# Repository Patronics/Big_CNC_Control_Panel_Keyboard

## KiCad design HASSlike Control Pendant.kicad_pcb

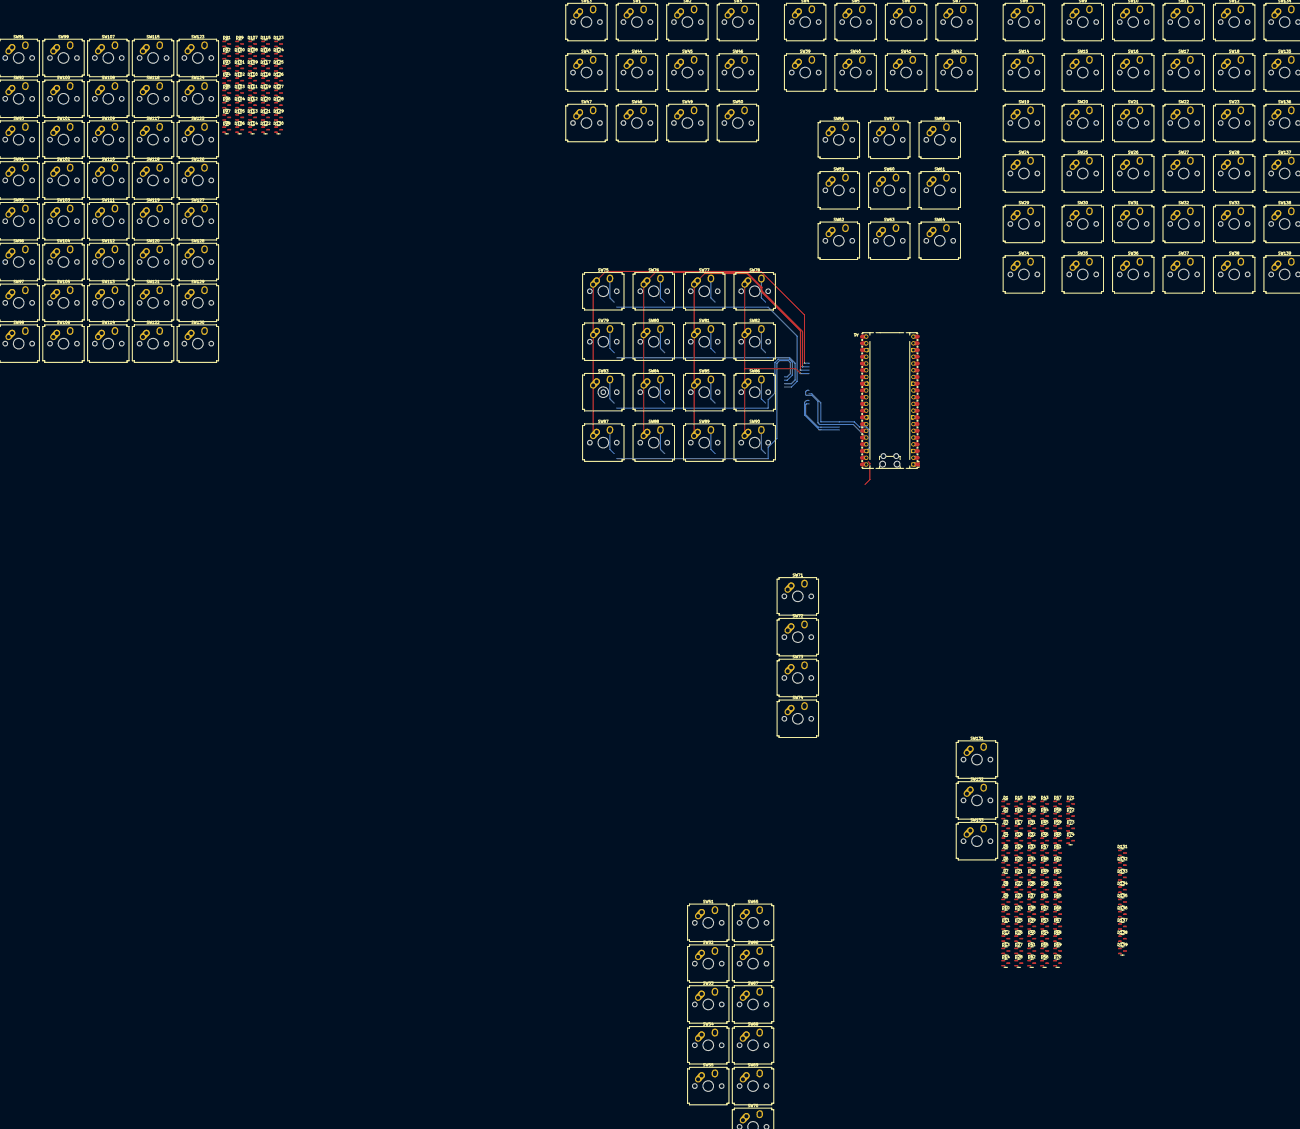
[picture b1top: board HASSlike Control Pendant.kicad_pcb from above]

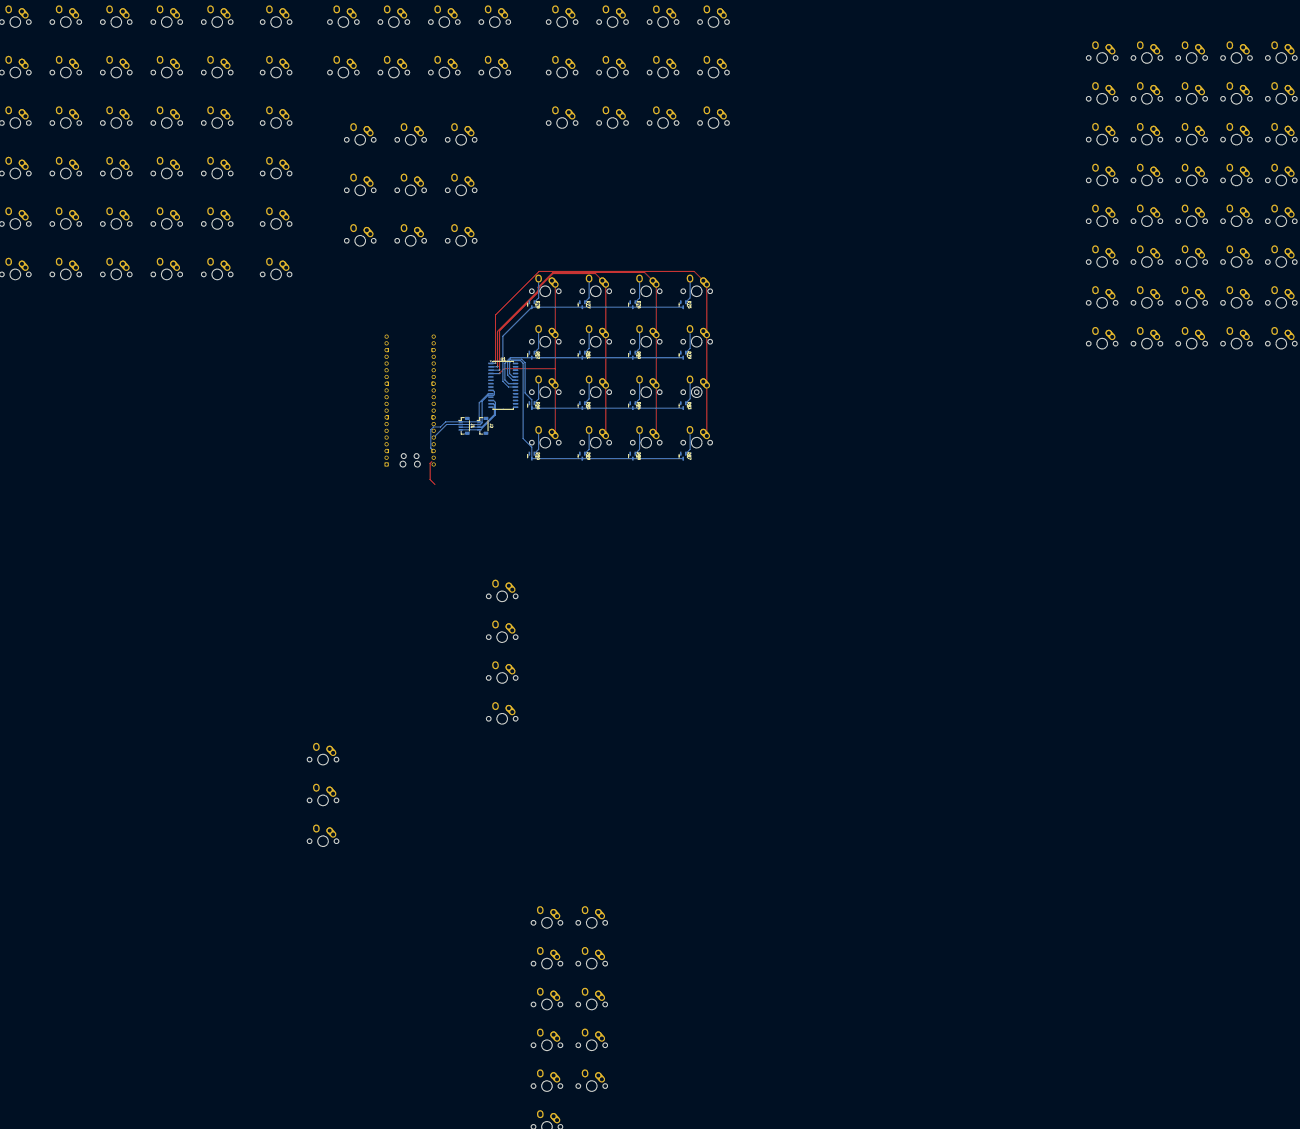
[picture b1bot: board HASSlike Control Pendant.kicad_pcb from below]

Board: 2 copper layers, 282 parts (19 on the bottom side), 184 nets.

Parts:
A1: RaspberryPi_Pico_W; RaspberryPi_Pico_Common_Unspecified
D1, D2, D3, D4, D5, D6, D7, D8, D9, D10, D11, D12, D13, D14, D15, D16, D17, D18, D19, D20, D21, D22, D23, D24, D25, D26, D27, D28, D29, D30, D31, D32, D33, D34, D35, D36, D37, D38, D39, D40, D41, D42, D43, D44, D45, D46, D47, D48, D49, D50, D51, D52, D53, D54, D55, D56, D57, D58, D59, D60, D61, D62, D63, D64, D65, D66, D67, D68, D69, D70, D71, D72, D73, D74, D75, D76, D77, D78, D79, D80, D81, D82, D83, D84, D85, D86, D87, D88, D89, D90, D91, D92, D93, D94, D95, D96, D97, D98, D99, D100, D101, D102, D103, D104, D105, D106, D107, D108, D109, D110, D111, D112, D113, D114, D115, D116, D117, D118, D119, D120, D121, D122, D123, D124, D125, D126, D127, D128, D129, D130, D131, D132, D133, D134, D135, D136, D137, D138, D139: D_Small; D_SOT-23_MMDB4148_BAS21_BAT54
J1, J2: Conn_01x04_Pin; JST_SH_BM04B-SRSS-TB_1x04-1MP_P1.00mm_Vertical
SW1, SW2, SW3, SW4, SW5, SW6, SW7, SW8, SW9, SW10, SW11, SW12, SW13, SW14, SW15, SW16, SW17, SW18, SW19, SW20, SW21, SW22, SW23, SW24, SW25, SW26, SW27, SW28, SW29, SW30, SW31, SW32, SW33, SW34, SW35, SW36, SW37, SW38, SW39, SW40, SW41, SW42, SW43, SW44, SW45, SW46, SW47, SW48, SW49, SW50, SW51, SW52, SW53, SW54, SW55, SW56, SW57, SW58, SW59, SW60, SW61, SW62, SW63, SW64, SW65, SW66, SW67, SW68, SW69, SW70, SW71, SW72, SW73, SW74, SW75, SW76, SW77, SW78, SW79, SW80, SW81, SW82, SW83, SW84, SW85, SW86, SW87, SW88, SW89, SW90, SW91, SW92, SW93, SW94, SW95, SW96, SW97, SW98, SW99, SW100, SW101, SW102, SW103, SW104, SW105, SW106, SW107, SW108, SW109, SW110, SW111, SW112, SW113, SW114, SW115, SW116, SW117, SW118, SW119, SW120, SW121, SW122, SW123, SW124, SW125, SW126, SW127, SW128, SW129, SW130, SW131, SW132, SW133, SW134, SW135, SW136, SW137, SW138, SW139: SW_Push; SW_Hybrid_Cherry_MX_Alps_1.00u
U1: MCP23017_SO; SOIC-28W_7.5x17.9mm_P1.27mm

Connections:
/4x4Test/Col1: SW75.1, SW79.1, SW83.1, SW87.1, U1.1 (GPB0)
/4x4Test/Col2: SW76.1, SW80.1, SW84.1, SW88.1, U1.2 (GPB1)
/4x4Test/Col3: SW77.1, SW81.1, SW85.1, SW89.1, U1.3 (GPB2)
/4x4Test/Col4: SW78.1, SW82.1, SW86.1, SW90.1, U1.4 (GPB3)
/4x4Test/Row1: D75.1 (K), D76.1 (K), D77.1 (K), D78.1 (K), U1.21 (GPA0)
/4x4Test/Row2: D79.1 (K), D80.1 (K), D81.1 (K), D82.1 (K), U1.22 (GPA1)
/4x4Test/Row3: D83.1 (K), D84.1 (K), D85.1 (K), D86.1 (K), U1.23 (GPA2)
/4x4Test/Row4: D87.1 (K), D88.1 (K), D89.1 (K), D90.1 (K), U1.24 (GPA3)
/SCL: J1.4, J2.4, U1.12 (SCK)
/SDA: J1.3, J2.3, U1.13 (SDA)
COL1: SW13.1, SW43.1, SW47.1, SW51.1, SW65.1, SW70.1
COL2: SW1.1, SW44.1, SW48.1, SW52.1, SW66.1, SW71.1
COL3: SW2.1, SW45.1, SW49.1, SW53.1, SW67.1, SW72.1
COL4: SW3.1, SW46.1, SW50.1, SW54.1, SW68.1, SW73.1
COL5: SW4.1, SW39.1, SW55.1, SW69.1, SW74.1
COL6: SW5.1, SW40.1, SW56.1, SW59.1, SW62.1, SW131.1
COL7: SW6.1, SW41.1, SW57.1, SW60.1, SW63.1, SW132.1
COL8: SW7.1, SW42.1, SW58.1, SW61.1, SW64.1, SW133.1
COL9: SW8.1, SW14.1, SW19.1, SW24.1, SW29.1, SW34.1
COL10: SW9.1, SW15.1, SW20.1, SW25.1, SW30.1, SW35.1
COL11: SW10.1, SW16.1, SW21.1, SW26.1, SW31.1, SW36.1
COL12: SW11.1, SW17.1, SW22.1, SW27.1, SW32.1, SW37.1
COL13: SW12.1, SW18.1, SW23.1, SW28.1, SW33.1, SW38.1
COL14: SW134.1, SW135.1, SW136.1, SW137.1, SW138.1, SW139.1
GND: A1.3 (GND), A1.8 (GND), A1.13 (GND), A1.18 (GND), A1.23 (GND), A1.28 (GND), A1.38 (GND), J1.1, J2.1, U1.10 (VSS)
unnamed: D1.2 (A), SW13.2
unnamed: D2.2 (A), SW1.2
unnamed: D3.2 (A), SW2.2
unnamed: D4.2 (A), SW3.2
unnamed: D5.2 (A), SW4.2
unnamed: D6.2 (A), SW5.2
unnamed: D7.2 (A), SW6.2
unnamed: D8.2 (A), SW7.2
unnamed: D9.2 (A), SW8.2
unnamed: D10.2 (A), SW9.2
unnamed: D11.2 (A), SW10.2
unnamed: D12.2 (A), SW11.2
unnamed: D13.2 (A), SW12.2
unnamed: D14.2 (A), SW14.2
unnamed: D15.2 (A), SW15.2
unnamed: D16.2 (A), SW16.2
unnamed: D17.2 (A), SW17.2
unnamed: D18.2 (A), SW18.2
unnamed: D19.2 (A), SW19.2
unnamed: D20.2 (A), SW20.2
unnamed: D21.2 (A), SW21.2
unnamed: D22.2 (A), SW22.2
unnamed: D23.2 (A), SW23.2
unnamed: D24.2 (A), SW24.2
unnamed: D25.2 (A), SW25.2
unnamed: D26.2 (A), SW26.2
unnamed: D27.2 (A), SW27.2
unnamed: D28.2 (A), SW28.2
unnamed: D29.2 (A), SW29.2
unnamed: D30.2 (A), SW30.2
unnamed: D31.2 (A), SW31.2
unnamed: D32.2 (A), SW32.2
unnamed: D33.2 (A), SW33.2
unnamed: D34.2 (A), SW34.2
unnamed: D35.2 (A), SW35.2
unnamed: D36.2 (A), SW36.2
unnamed: D37.2 (A), SW37.2
unnamed: D38.2 (A), SW38.2
unnamed: D39.2 (A), SW39.2
unnamed: D40.2 (A), SW40.2
unnamed: D41.2 (A), SW41.2
unnamed: D42.2 (A), SW42.2
unnamed: D43.2 (A), SW43.2
unnamed: D44.2 (A), SW44.2
unnamed: D45.2 (A), SW45.2
unnamed: D46.2 (A), SW46.2
unnamed: D47.2 (A), SW47.2
unnamed: D48.2 (A), SW48.2
unnamed: D49.2 (A), SW49.2
unnamed: D50.2 (A), SW50.2
unnamed: D51.2 (A), SW51.2
unnamed: D52.2 (A), SW52.2
unnamed: D53.2 (A), SW53.2
unnamed: D54.2 (A), SW54.2
unnamed: D55.2 (A), SW55.2
unnamed: D56.2 (A), SW56.2
unnamed: D57.2 (A), SW57.2
unnamed: D58.2 (A), SW58.2
unnamed: D59.2 (A), SW59.2
unnamed: D60.2 (A), SW60.2
unnamed: D61.2 (A), SW61.2
unnamed: D62.2 (A), SW62.2
unnamed: D63.2 (A), SW63.2
unnamed: D64.2 (A), SW64.2
unnamed: D65.2 (A), SW65.2
unnamed: D66.2 (A), SW66.2
unnamed: D67.2 (A), SW67.2
unnamed: D68.2 (A), SW68.2
unnamed: D69.2 (A), SW69.2
unnamed: D70.2 (A), SW70.2
unnamed: D71.2 (A), SW71.2
unnamed: D72.2 (A), SW72.2
unnamed: D73.2 (A), SW73.2
unnamed: D74.2 (A), SW74.2
unnamed: D75.2 (A), SW75.2
unnamed: D76.2 (A), SW76.2
unnamed: D77.2 (A), SW77.2
unnamed: D78.2 (A), SW78.2
unnamed: D79.2 (A), SW79.2
unnamed: D80.2 (A), SW80.2
unnamed: D81.2 (A), SW81.2
unnamed: D82.2 (A), SW82.2
unnamed: D83.2 (A), SW83.2
unnamed: D84.2 (A), SW84.2
unnamed: D85.2 (A), SW85.2
unnamed: D86.2 (A), SW86.2
unnamed: D87.2 (A), SW87.2
unnamed: D88.2 (A), SW88.2
unnamed: D89.2 (A), SW89.2
unnamed: D90.2 (A), SW90.2
unnamed: D91.2 (A), SW91.2
unnamed: D92.2 (A), SW92.2
unnamed: D93.2 (A), SW93.2
unnamed: D94.2 (A), SW94.2
unnamed: D95.2 (A), SW95.2
unnamed: D96.2 (A), SW96.2
unnamed: D97.2 (A), SW97.2
unnamed: D98.2 (A), SW98.2
unnamed: D99.2 (A), SW99.2
unnamed: D100.2 (A), SW100.2
unnamed: D91.1 (K), D92.1 (K), D93.1 (K), D94.1 (K), D95.1 (K), D96.1 (K), D97.1 (K), D98.1 (K), D99.1 (K), D100.1 (K)
unnamed: D101.2 (A), SW101.2
unnamed: D101.1 (K), D102.1 (K), D103.1 (K), D104.1 (K), D105.1 (K), D106.1 (K), D107.1 (K), D108.1 (K), D109.1 (K), D110.1 (K)
unnamed: D102.2 (A), SW102.2
unnamed: D103.2 (A), SW103.2
unnamed: D104.2 (A), SW104.2
unnamed: D105.2 (A), SW105.2
unnamed: D106.2 (A), SW106.2
unnamed: D107.2 (A), SW107.2
unnamed: D108.2 (A), SW108.2
unnamed: D109.2 (A), SW109.2
unnamed: D110.2 (A), SW110.2
unnamed: D111.2 (A), SW111.2
unnamed: D111.1 (K), D112.1 (K), D113.1 (K), D114.1 (K), D115.1 (K), D116.1 (K), D117.1 (K), D118.1 (K), D119.1 (K), D120.1 (K)
unnamed: D112.2 (A), SW112.2
unnamed: D113.2 (A), SW113.2
unnamed: D114.2 (A), SW114.2
unnamed: D115.2 (A), SW115.2
unnamed: D116.2 (A), SW116.2
unnamed: D117.2 (A), SW117.2
unnamed: D118.2 (A), SW118.2
unnamed: D119.2 (A), SW119.2
unnamed: D120.2 (A), SW120.2
unnamed: D121.2 (A), SW121.2
unnamed: D121.1 (K), D122.1 (K), D123.1 (K), D124.1 (K), D125.1 (K), D126.1 (K), D127.1 (K), D128.1 (K), D129.1 (K), D130.1 (K)
unnamed: D122.2 (A), SW122.2
unnamed: D123.2 (A), SW123.2
unnamed: D124.2 (A), SW124.2
unnamed: D125.2 (A), SW125.2
unnamed: D126.2 (A), SW126.2
unnamed: D127.2 (A), SW127.2
unnamed: D128.2 (A), SW128.2
unnamed: D129.2 (A), SW129.2
unnamed: D130.2 (A), SW130.2
unnamed: D131.2 (A), SW131.2
unnamed: D132.2 (A), SW132.2
unnamed: D133.2 (A), SW133.2
unnamed: D134.2 (A), SW134.2
unnamed: D135.2 (A), SW135.2
unnamed: D136.2 (A), SW136.2
unnamed: D137.2 (A), SW137.2
unnamed: D138.2 (A), SW138.2
unnamed: D139.2 (A), SW139.2
unnamed: SW100.1, SW110.1, SW120.1, SW130.1
unnamed: SW92.1, SW102.1, SW112.1, SW122.1
unnamed: SW93.1, SW103.1, SW113.1, SW123.1
unnamed: SW94.1, SW104.1, SW114.1, SW124.1
unnamed: SW95.1, SW105.1, SW115.1, SW125.1
unnamed: SW96.1, SW106.1, SW116.1, SW126.1
unnamed: SW97.1, SW107.1, SW117.1, SW127.1
unnamed: SW98.1, SW108.1, SW118.1, SW128.1
unnamed: SW99.1, SW109.1, SW119.1, SW129.1
ROW1: D1.1 (K), D2.1 (K), D3.1 (K), D4.1 (K), D5.1 (K), D6.1 (K), D7.1 (K), D8.1 (K), D9.1 (K), D10.1 (K), D11.1 (K), D12.1 (K), D13.1 (K), D134.1 (K)
ROW2: D14.1 (K), D15.1 (K), D16.1 (K), D17.1 (K), D18.1 (K), D39.1 (K), D40.1 (K), D41.1 (K), D42.1 (K), D43.1 (K), D44.1 (K), D45.1 (K), D46.1 (K), D135.1 (K)
ROW3: D19.1 (K), D20.1 (K), D21.1 (K), D22.1 (K), D23.1 (K), D47.1 (K), D48.1 (K), D49.1 (K), D50.1 (K), D56.1 (K), D57.1 (K), D58.1 (K), D136.1 (K)
ROW4: D24.1 (K), D25.1 (K), D26.1 (K), D27.1 (K), D28.1 (K), D51.1 (K), D52.1 (K), D53.1 (K), D54.1 (K), D55.1 (K), D137.1 (K)
ROW5: D29.1 (K), D30.1 (K), D31.1 (K), D32.1 (K), D33.1 (K), D62.1 (K), D63.1 (K), D64.1 (K), D65.1 (K), D66.1 (K), D67.1 (K), D68.1 (K), D69.1 (K), D138.1 (K)
ROW6: D34.1 (K), D35.1 (K), D36.1 (K), D37.1 (K), D38.1 (K), D70.1 (K), D71.1 (K), D72.1 (K), D73.1 (K), D74.1 (K), D131.1 (K), D132.1 (K), D133.1 (K), D139.1 (K)
VCC: A1.36 (3V3), J1.2, J2.2, U1.9 (VDD)

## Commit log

2025-03-17 initial commit, establish basic key layout
2025-03-19 start on pcb layout for monolithic implementation
2025-03-19 progress on layout for small-scale proof of concept board
